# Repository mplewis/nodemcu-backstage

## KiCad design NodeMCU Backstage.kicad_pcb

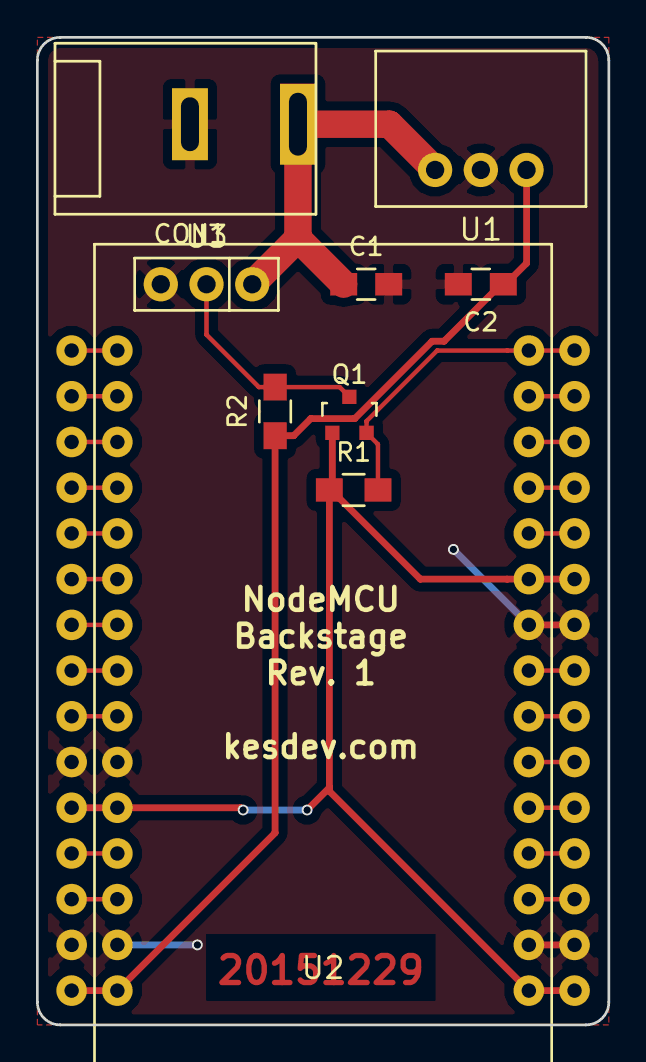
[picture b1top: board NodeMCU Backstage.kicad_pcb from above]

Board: 2 copper layers, 31.8 x 54.9 mm, 9 parts (0 on the bottom side), 6 nets.

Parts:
C1, C2: 10µF; C_0805_HandSoldering
CON1: BARREL_JACK_NO_SW; PJ-037A
Q1: BSS138; SOT-23
R1, R2: 10K; R_0805_HandSoldering
U1: R-78E5.0-0.5
U2: NODEMCU_AMICA; NODEMCU_AMICA_WIDE
U3: HEADER_WS2812; SIP-3

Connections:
+3V3: Q1.1, R1.1, U2.11, U2.16, U2.25
+5V: C2.1, R2.1, U1.3, U2.15
+12V: C1.1, CON1.1, U1.1, U3.1
D0_5V: Q1.3, R2.2, U3.2
GND: C1.2, C2.2, CON1.2, U1.2, U2.10, U2.14, U2.17, U2.24, U3.3
unnamed: Q1.2, R1.2, U2.30

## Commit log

2015-12-29 git: initial commit
2015-12-29 release: rev 1
2015-12-30 rev2: better silk labels, switch to vias not slot barrel solder
